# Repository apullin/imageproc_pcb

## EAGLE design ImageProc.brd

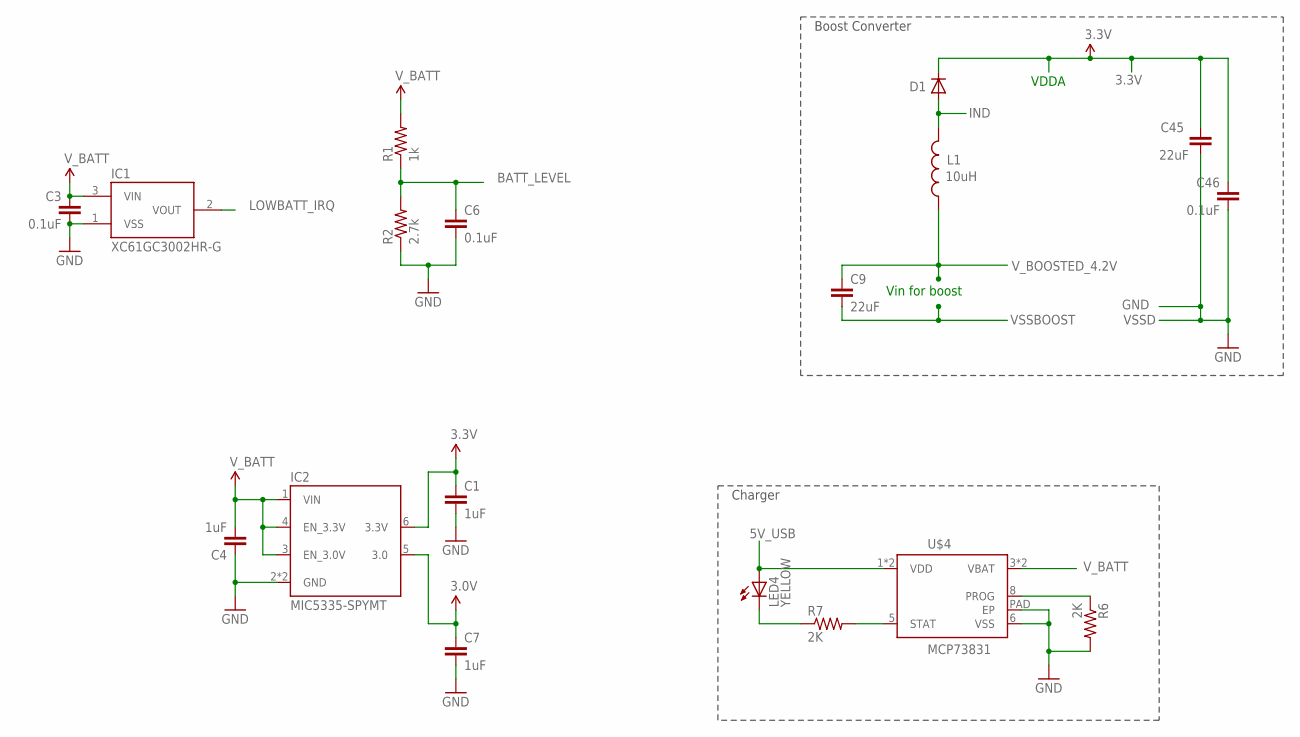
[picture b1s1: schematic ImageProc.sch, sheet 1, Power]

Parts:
C1, C4, C7: 1uF; 0402-CAP
C3, C6, C46: 0.1uF; 0402-CAP
C9, C45: 22uF; 0805
D1: DIODE-SOD123; SOD123
IC1: XC61GC3002HR-G; USP-3
IC2: MIC5335-SPYMT; MLF-6
L1: 10uH; INDUCTOR_SMD_3X3
LED4: YELLOW; LED-0603
R1: 1k; 0402-RES
R2: 2.7k; 0402-RES
R6, R7: 2K; 0402-RES
U$4: MCP73831; DFN-8

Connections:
3.0V: C7.1, IC2.5 (3.0)
3.3V: C1.1, C45.1, C46.1, D1.C, IC2.6 (3.3V); also elsewhere on the board
5V_USB: LED4.A, U$4.1 (VDD), U$4.2 (VDD); also elsewhere on the board
BATT_LEVEL: C6.1, R1.1, R2.2; also elsewhere on the board
GND: C1.2, C3.2, C4.1, C6.2, C7.2, C45.2, C46.2, IC1.1 (VSS), IC2.2 (GND), IC2.EPAD (GND), R2.1, R6.2, U$4.6 (VSS), U$4.PAD (EP); also elsewhere on the board
IND: D1.A, L1.P$2 (2); also elsewhere on the board
LOWBATT_IRQ: IC1.2 (VOUT)
unnamed: R6.1, U$4.8 (PROG)
unnamed: LED4.C, R7.1
unnamed: R7.2, U$4.5 (STAT)
VSSBOOST: C9.2; also elsewhere on the board
V_BATT: C3.1, C4.2, IC1.3 (VIN), IC2.1 (VIN), IC2.3 (EN_3.0V), IC2.4 (EN_3.3V), R1.2, U$4.3 (VBAT), U$4.4 (VBAT); also elsewhere on the board
V_BOOSTED_4.2V: C9.1, L1.P$1 (1); also elsewhere on the board

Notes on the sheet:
Vin for boost
VSSD
VDDA
Boost Converter
Charger

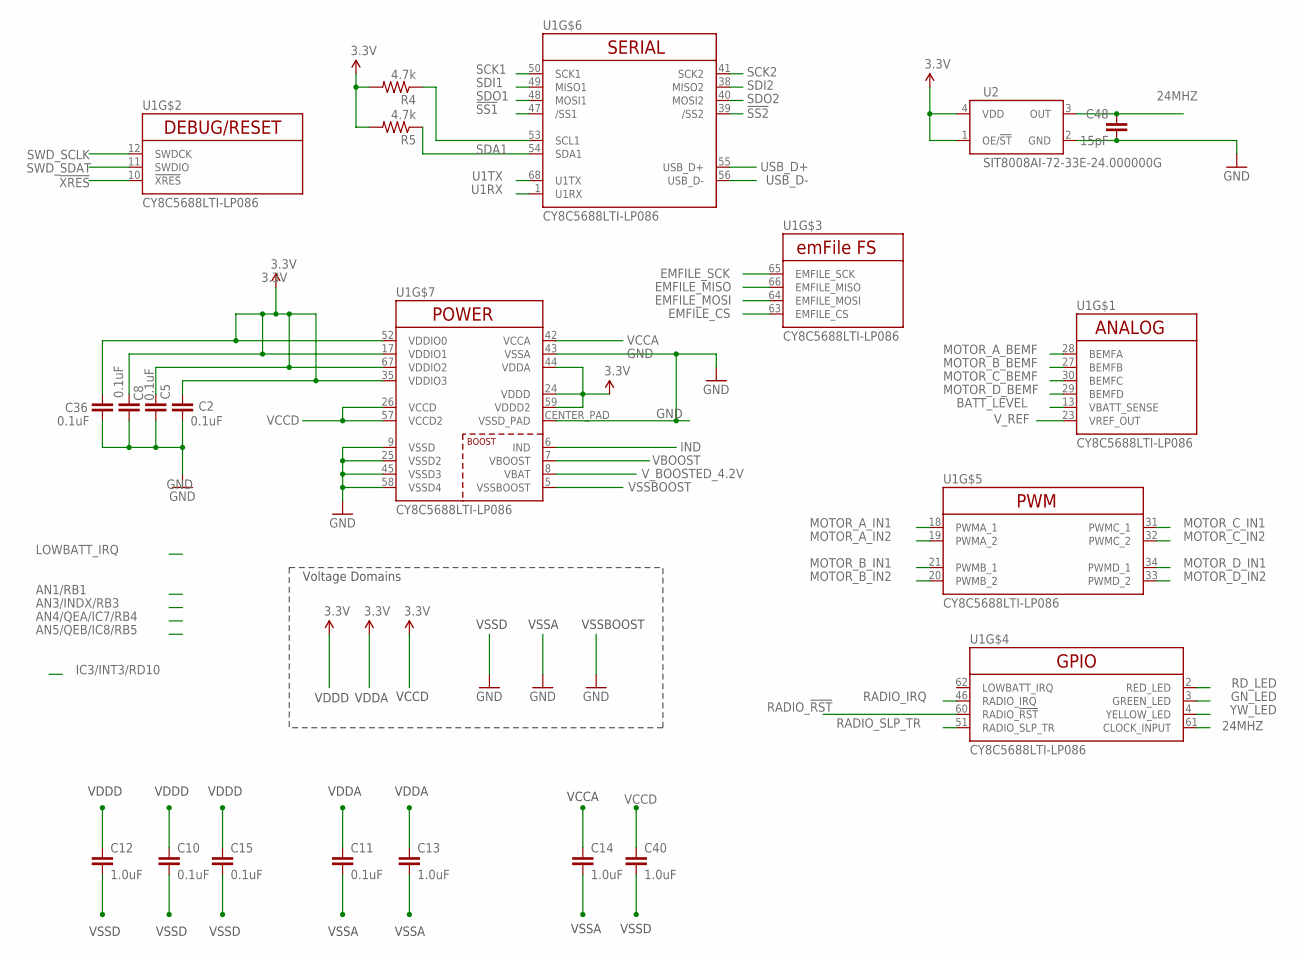
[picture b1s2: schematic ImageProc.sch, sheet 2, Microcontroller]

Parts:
C2, C5, C8, C10, C11, C15, C36: 0.1uF; 0402-CAP
C12, C13, C14, C40: 1.0uF; 0402-CAP
C48: 15pF; 0402-CAP; TOLERANCE 5%; VOLTAGE 50V
R4, R5: 4.7k; 0402-RES
U1: CY8C5688LTI-LP086; 68QFN
U2: SIT8008AI-72-33E-24.000000G; 4-SMD

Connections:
3.3V: C2.1, C5.1, C8.1, C10.1, C11.1, C12.1, C13.1, C15.1, C36.1, R4.2, R5.2, U1.17 (VDDIO1), U1.24 (VDDD), U1.35 (VDDIO3), U1.44 (VDDA), U1.52 (VDDIO0), U1.59 (VDDD2), U1.67 (VDDIO2), U2.1 (OE/!ST), U2.4 (VDD); also elsewhere on the board
24MHZ: C48.1, U1.61 (CLOCK_INPUT), U2.3 (OUT)
!SS1: U1.47 (/SS1); also elsewhere on the board
!SS2: U1.39 (/SS2); also elsewhere on the board
!XRES: U1.10 (!XRES); also elsewhere on the board
BATT_LEVEL: U1.13 (VBATT_SENSE); also elsewhere on the board
EMFILE_CS: U1.63 (EMFILE_CS); also elsewhere on the board
EMFILE_MISO: U1.66 (EMFILE_MISO); also elsewhere on the board
EMFILE_MOSI: U1.64 (EMFILE_MOSI); also elsewhere on the board
EMFILE_SCK: U1.65 (EMFILE_SCK); also elsewhere on the board
GND: C2.2, C5.2, C8.2, C10.2, C11.2, C12.2, C14.2, C15.2, C36.2, C40.2, C48.2, U1.9 (VSSD), U1.25 (VSSD2), U1.43 (VSSA), U1.45 (VSSD3), U1.58 (VSSD4), U1.CENTER_PAD (VSSD_PAD), U2.2 (GND); also elsewhere on the board
GN_LED: U1.3 (GREEN_LED); also elsewhere on the board
IND: U1.6 (IND); also elsewhere on the board
MOTOR_A_BEMF: U1.28 (BEMFA); also elsewhere on the board
MOTOR_A_IN1: U1.18 (PWMA_1); also elsewhere on the board
MOTOR_A_IN2: U1.19 (PWMA_2); also elsewhere on the board
MOTOR_B_BEMF: U1.27 (BEMFB); also elsewhere on the board
MOTOR_B_IN1: U1.21 (PWMB_1); also elsewhere on the board
MOTOR_B_IN2: U1.20 (PWMB_2); also elsewhere on the board
MOTOR_C_BEMF: U1.30 (BEMFC); also elsewhere on the board
MOTOR_C_IN1: U1.31 (PWMC_1); also elsewhere on the board
MOTOR_C_IN2: U1.32 (PWMC_2); also elsewhere on the board
MOTOR_D_BEMF: U1.29 (BEMFD); also elsewhere on the board
MOTOR_D_IN1: U1.34 (PWMD_1); also elsewhere on the board
MOTOR_D_IN2: U1.33 (PWMD_2); also elsewhere on the board
RADIO_!RST: U1.60 (RADIO_!RST); also elsewhere on the board
RADIO_IRQ: U1.46 (RADIO_IRQ); also elsewhere on the board
RADIO_SLP_TR: U1.51 (RADIO_SLP_TR); also elsewhere on the board
RD_LED: U1.2 (RED_LED); also elsewhere on the board
SCK1: U1.50 (SCK1); also elsewhere on the board
SCK2: U1.41 (SCK2); also elsewhere on the board
SCL1: R4.1, U1.53 (SCL1); also elsewhere on the board
SDA1: R5.1, U1.54 (SDA1); also elsewhere on the board
SDI1: U1.49 (MISO1); also elsewhere on the board
SDI2: U1.38 (MISO2); also elsewhere on the board
SDO1: U1.48 (MOSI1); also elsewhere on the board
SDO2: U1.40 (MOSI2); also elsewhere on the board
SWD_SCLK: U1.12 (SWDCK); also elsewhere on the board
SWD_SDAT: U1.11 (SWDIO); also elsewhere on the board
U1RX: U1.1 (U1RX); also elsewhere on the board
U1TX: U1.68 (U1TX); also elsewhere on the board
USB_D+: U1.55 (USB_D+); also elsewhere on the board
USB_D-: U1.56 (USB_D-); also elsewhere on the board
VBOOST: U1.7 (VBOOST)
VCCA: C14.1, U1.42 (VCCA)
VCCD: C40.1, U1.26 (VCCD), U1.57 (VCCD2)
VSSA: C13.2
VSSBOOST: U1.5 (VSSBOOST); also elsewhere on the board
V_BOOSTED_4.2V: U1.8 (VBAT); also elsewhere on the board
V_REF: U1.23 (VREF_OUT); also elsewhere on the board
YW_LED: U1.4 (YELLOW_LED); also elsewhere on the board

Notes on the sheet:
Voltage Domains
VSSA
VSSD
VDDD
VDDA
VCCD
VSSBOOST
VCCA

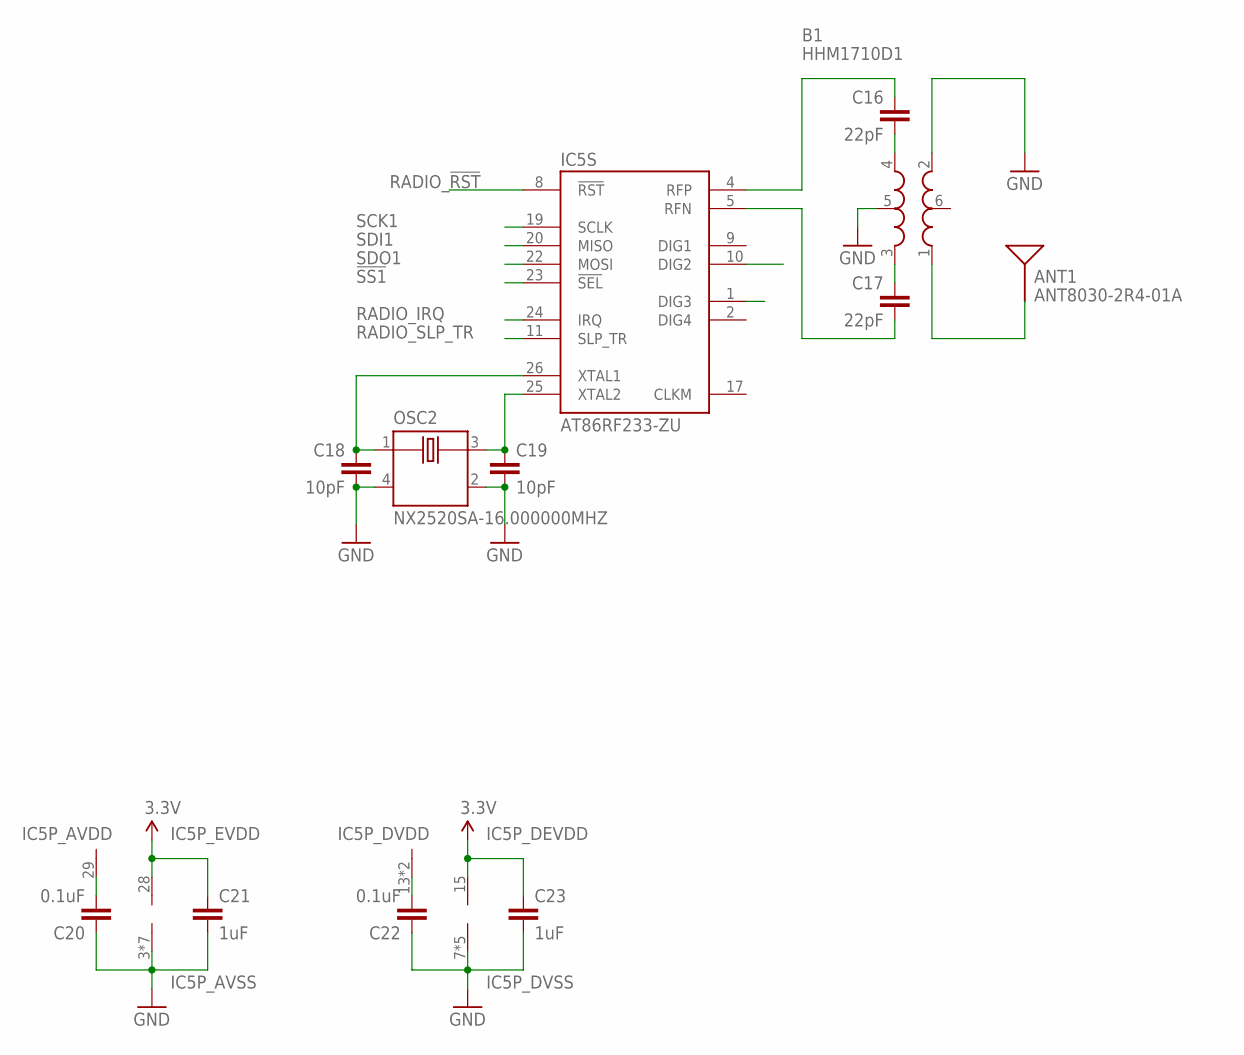
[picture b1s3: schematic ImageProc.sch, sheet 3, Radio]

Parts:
ANT1: ANT8030-2R4-01A
B1: HHM1710D1; 0603-BALUN
C16, C17: 22pF; 0402-CAP; TOLERANCE 5%; VOLTAGE 50V
C18, C19: 10pF; 0402-CAP; TOLERANCE 10%; VOLTAGE 50V
C20, C22: 0.1uF; 0402-CAP; TOLERANCE 10%; VOLTAGE 16V
C21, C23: 1uF; 0402-CAP; TOLERANCE 10%; VOLTAGE 16V
IC5: AT86RF233-ZU; VQFN-32QN2
OSC2: NX2520SA-16.000000MHZ; CRYSTAL-SMD

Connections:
3.3V: C21.1, C23.1, IC5.15 (V+), IC5.28 (V+); also elsewhere on the board
!SS1: IC5.23 (!SEL); also elsewhere on the board
GND: B1.2 (RFGND), B1.5 (GND), C18.2, C19.2, C20.1, C21.2, C22.1, C23.2, IC5.3 (V-), IC5.6 (V-), IC5.7 (V-), IC5.12 (V-), IC5.16 (V-), IC5.18 (V-), IC5.21 (V-), IC5.27 (V-), IC5.30 (V-), IC5.31 (V-), IC5.32 (V-), IC5.PAD (V-), OSC2.2 (GND), OSC2.4 (GND); also elsewhere on the board
unnamed: C22.2, IC5.13 (V+), IC5.14 (V+)
unnamed: C20.2, IC5.29 (V+)
unnamed: ANT1.A, B1.1 (UNBAL)
unnamed: C16.1, IC5.4 (RFP)
unnamed: C17.2, IC5.5 (RFN)
unnamed: C19.1, IC5.25 (XTAL2), OSC2.3 (OUT/IN)
unnamed: C18.1, IC5.26 (XTAL1), OSC2.1 (IN/OUT)
unnamed: B1.3 (BAL3), C17.1
unnamed: B1.4 (BAL4), C16.2
RADIO_!RST: IC5.8 (!RST); also elsewhere on the board
RADIO_IRQ: IC5.24 (IRQ); also elsewhere on the board
RADIO_SLP_TR: IC5.11 (SLP_TR); also elsewhere on the board
SCK1: IC5.19 (SCLK); also elsewhere on the board
SDI1: IC5.20 (MISO); also elsewhere on the board
SDO1: IC5.22 (MOSI); also elsewhere on the board

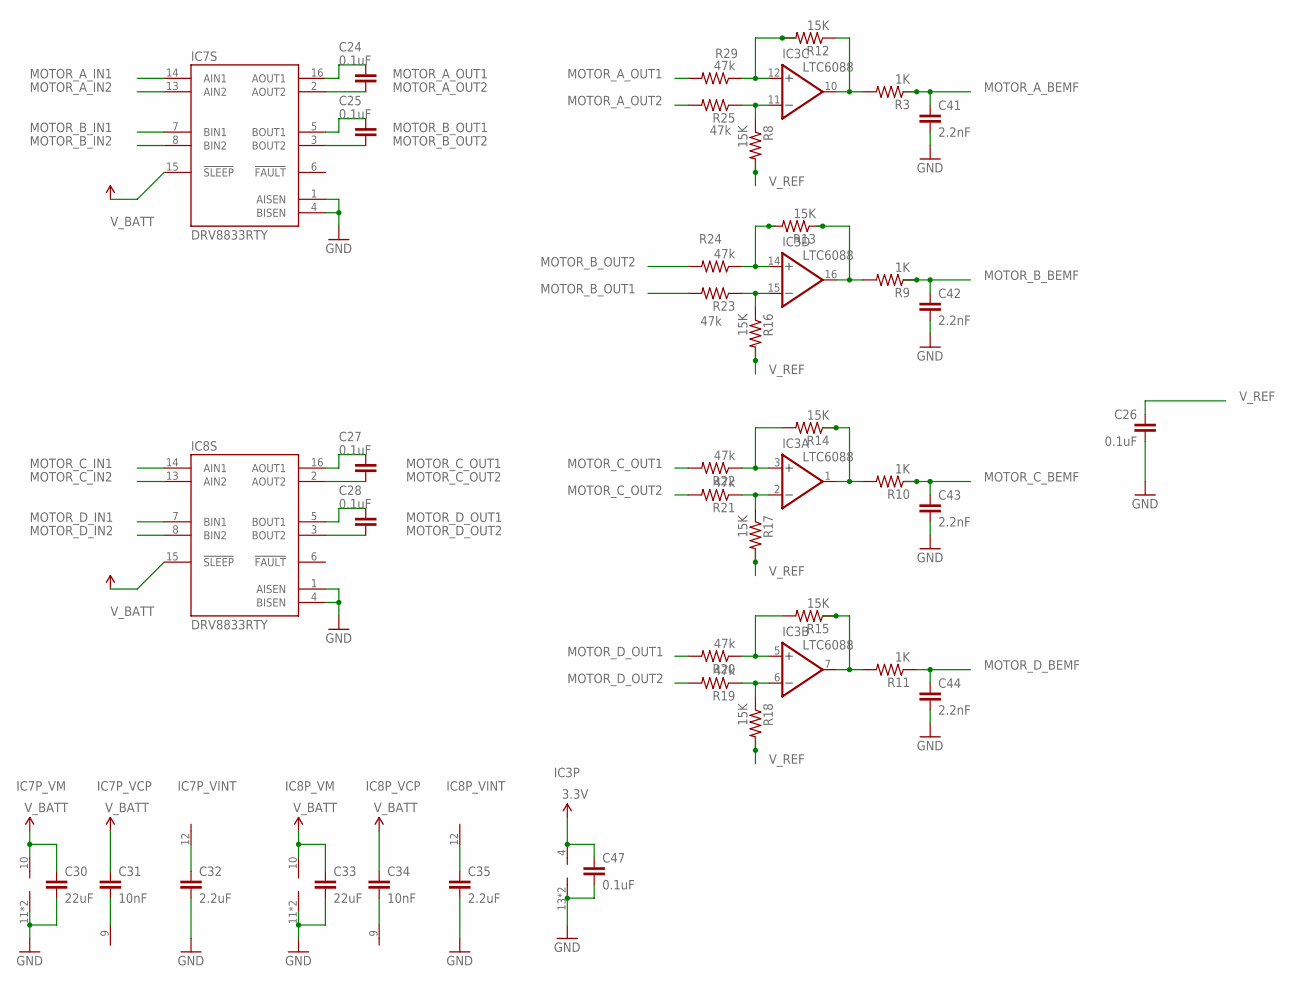
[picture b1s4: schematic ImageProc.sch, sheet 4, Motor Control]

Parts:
C24, C25, C27, C28: 0.1uF; 0402-CAP; VOLTAGE 10V
C26, C47: 0.1uF; 0402-CAP
C30, C33: 22uF; 0603-CAP
C31, C34: 10nF; 0402-CAP; VOLTAGE 16V
C32, C35: 2.2uF; 0402-CAP; VOLTAGE 6.3V
C41, C42, C43, C44: 2.2nF; 0402-CAP
IC3: LTC6088; DFN-16
IC7, IC8: DRV8833RTY; S-PWQFN-N16
R3, R9, R10, R11: 1K; 0402-RES
R8, R12, R13, R14, R15, R16, R17, R18: 15K; 0402-RES
R19, R20, R21, R22, R23, R24, R25, R29: 47k; 0402-RES

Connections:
3.3V: C47.1, IC3.4 (V+); also elsewhere on the board
GND: C26.2, C30.2, C32.2, C33.2, C35.2, C41.2, C42.2, C43.2, C44.2, C47.2, IC3.13 (V-), IC3.PAD (V-), IC7.1 (AISEN), IC7.4 (BISEN), IC7.11 (V-), IC7.PPAD (V-), IC8.1 (AISEN), IC8.4 (BISEN), IC8.11 (V-), IC8.PPAD (V-); also elsewhere on the board
MOTOR_A_BEMF: C41.1, R3.1; also elsewhere on the board
MOTOR_A_IN1: IC7.14 (AIN1); also elsewhere on the board
MOTOR_A_IN2: IC7.13 (AIN2); also elsewhere on the board
MOTOR_A_OUT1: C24.1, IC7.16 (AOUT1), R29.2; also elsewhere on the board
MOTOR_A_OUT2: C24.2, IC7.2 (AOUT2), R25.2; also elsewhere on the board
MOTOR_B_BEMF: C42.1, R9.1; also elsewhere on the board
MOTOR_B_IN1: IC7.7 (BIN1); also elsewhere on the board
MOTOR_B_IN2: IC7.8 (BIN2); also elsewhere on the board
MOTOR_B_OUT1: C25.1, IC7.5 (BOUT1), R23.2; also elsewhere on the board
MOTOR_B_OUT2: C25.2, IC7.3 (BOUT2), R24.2; also elsewhere on the board
MOTOR_C_BEMF: C43.1, R10.1; also elsewhere on the board
MOTOR_C_IN1: IC8.14 (AIN1); also elsewhere on the board
MOTOR_C_IN2: IC8.13 (AIN2); also elsewhere on the board
MOTOR_C_OUT1: C27.1, IC8.16 (AOUT1), R22.2; also elsewhere on the board
MOTOR_C_OUT2: C27.2, IC8.2 (AOUT2), R21.2; also elsewhere on the board
MOTOR_D_BEMF: C44.1, R11.1; also elsewhere on the board
MOTOR_D_IN1: IC8.7 (BIN1); also elsewhere on the board
MOTOR_D_IN2: IC8.8 (BIN2); also elsewhere on the board
MOTOR_D_OUT1: C28.1, IC8.5 (BOUT1), R20.2; also elsewhere on the board
MOTOR_D_OUT2: C28.2, IC8.3 (BOUT2), R19.2; also elsewhere on the board
unnamed: C31.2, IC7.9 (V+)
unnamed: C32.1, IC7.12 (V-)
unnamed: C34.2, IC8.9 (V+)
unnamed: C35.1, IC8.12 (V-)
unnamed: IC3.14 (+IN), R13.2, R24.1
unnamed: IC3.15 (-IN), R16.1, R23.1
unnamed: IC3.3 (+IN), R14.2, R22.1
unnamed: IC3.2 (-IN), R17.1, R21.1
unnamed: IC3.5 (+IN), R15.2, R20.1
unnamed: IC3.6 (-IN), R18.1, R19.1
unnamed: IC3.12 (+IN), R12.2, R29.1
unnamed: IC3.11 (-IN), R8.1, R25.1
unnamed: IC3.7 (OUT), R11.2, R15.1
unnamed: IC3.1 (OUT), R10.2, R14.1
unnamed: IC3.10 (OUT), R3.2, R12.1
unnamed: IC3.16 (OUT), R9.2, R13.1
V_BATT: C30.1, C31.1, C33.1, C34.1, IC7.10 (V+), IC7.15 (!SLEEP), IC8.10 (V+), IC8.15 (!SLEEP); also elsewhere on the board
V_REF: C26.1, R8.2, R16.2, R17.2, R18.2; also elsewhere on the board

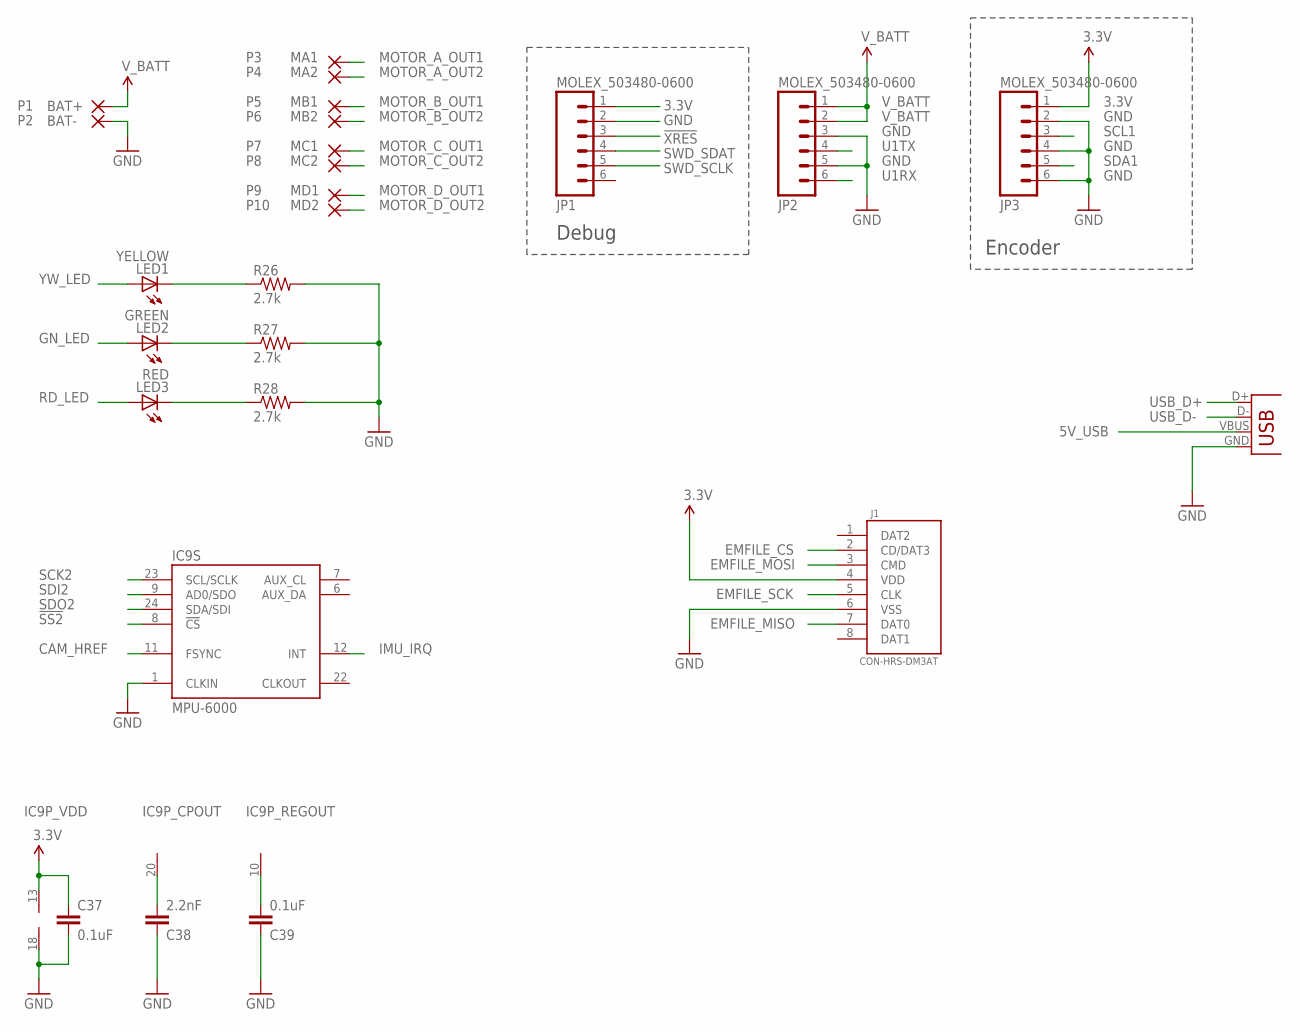
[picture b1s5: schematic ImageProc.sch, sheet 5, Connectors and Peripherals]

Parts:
C37: 0.1uF; 0402-CAP; TOLERANCE 10%; VOLTAGE 4V
C38: 2.2nF; 0402-CAP; TOLERANCE 10%; VOLTAGE 50V
C39: 0.1uF; 0402-CAP; TOLERANCE 10%; VOLTAGE 2V
IC9: MPU-6000; QFN-24
J1: CON-HRS-DM3AT; HRS-DM3AT
JP1, JP2, JP3: MOLEX_503480-0600
JP6: USBSMD; USB-MINIB
LED1: YELLOW; LED-0603
LED2: GREEN; LED-0603
LED3: RED; LED-0603
P1: BAT+; SMD1,27-2,54
P2: BAT-; SMD1,27-2,54
P3: MA1; SMD1,27-2,54
P4: MA2; SMD1,27-2,54
P5: MB1; SMD1,27-2,54
P6: MB2; SMD1,27-2,54
P7: MC1; SMD1,27-2,54
P8: MC2; SMD1,27-2,54
P9: MD1; SMD1,27-2,54
P10: MD2; SMD1,27-2,54
R26, R27, R28: 2.7k; 0402-RES

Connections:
3.3V: C37.1, IC9.13 (V+), J1.4 (VDD), JP1.1, JP3.1; also elsewhere on the board
5V_USB: JP6.VBUS; also elsewhere on the board
!SS2: IC9.8 (!CS); also elsewhere on the board
!XRES: JP1.3; also elsewhere on the board
CAM_HREF: IC9.11 (FSYNC)
EMFILE_CS: J1.2 (CD/DAT3); also elsewhere on the board
EMFILE_MISO: J1.7 (DAT0); also elsewhere on the board
EMFILE_MOSI: J1.3 (CMD); also elsewhere on the board
EMFILE_SCK: J1.5 (CLK); also elsewhere on the board
GND: C37.2, C38.1, C39.1, IC9.1 (CLKIN), IC9.18 (V-), J1.6 (VSS), JP1.2, JP2.3, JP2.5, JP3.2, JP3.4, JP3.6, JP6.GND, P2.1, R26.2, R27.2, R28.2; also elsewhere on the board
GN_LED: LED2.A; also elsewhere on the board
IMU_IRQ: IC9.12 (INT)
MOTOR_A_OUT1: P3.1; also elsewhere on the board
MOTOR_A_OUT2: P4.1; also elsewhere on the board
MOTOR_B_OUT1: P5.1; also elsewhere on the board
MOTOR_B_OUT2: P6.1; also elsewhere on the board
MOTOR_C_OUT1: P7.1; also elsewhere on the board
MOTOR_C_OUT2: P8.1; also elsewhere on the board
MOTOR_D_OUT1: P9.1; also elsewhere on the board
MOTOR_D_OUT2: P10.1; also elsewhere on the board
unnamed: LED1.C, R26.1
unnamed: LED2.C, R27.1
unnamed: LED3.C, R28.1
unnamed: C38.2, IC9.20 (V-)
unnamed: C39.2, IC9.10 (V-)
RD_LED: LED3.A; also elsewhere on the board
SCK2: IC9.23 (SCL/SCLK); also elsewhere on the board
SCL1: JP3.3; also elsewhere on the board
SDA1: JP3.5; also elsewhere on the board
SDI2: IC9.9 (AD0/SDO); also elsewhere on the board
SDO2: IC9.24 (SDA/SDI); also elsewhere on the board
SWD_SCLK: JP1.5; also elsewhere on the board
SWD_SDAT: JP1.4; also elsewhere on the board
U1RX: JP2.6; also elsewhere on the board
U1TX: JP2.4; also elsewhere on the board
USB_D+: JP6.D+; also elsewhere on the board
USB_D-: JP6.D-; also elsewhere on the board
V_BATT: JP2.1, JP2.2, P1.1; also elsewhere on the board
YW_LED: LED1.A; also elsewhere on the board

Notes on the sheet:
Encoder
Debug

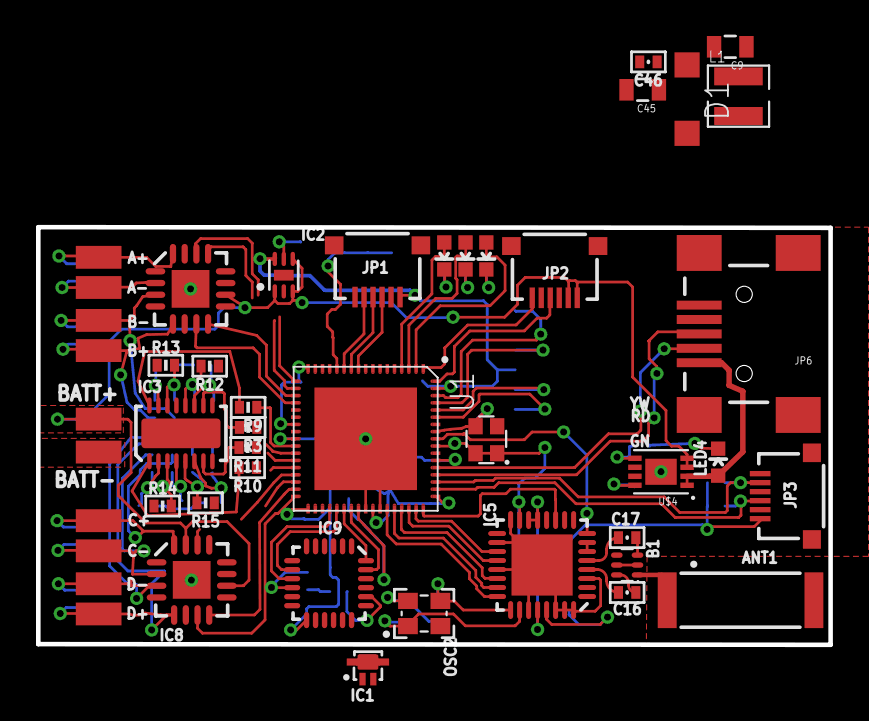
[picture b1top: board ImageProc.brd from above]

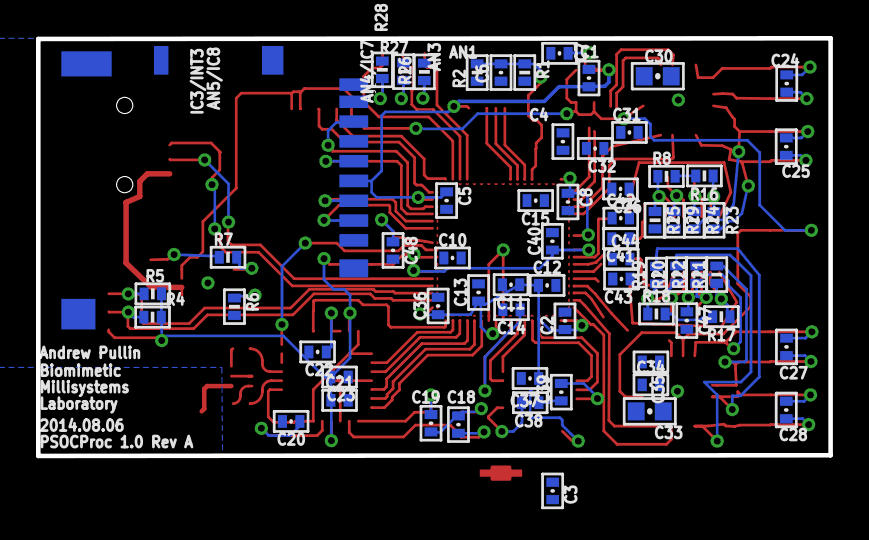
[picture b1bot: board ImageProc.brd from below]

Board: 2 copper layers, 44.0 x 23.2 mm, 110 parts (64 on the bottom side), 93 nets.

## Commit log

2014-07-16 Initial replacement of dsPIC with STM32 chip in schematic.
2014-08-06 Updating git ignore to not include doc folder
2014-08-06 Initial strip of the IP2.5 Rev C board. dsPic and camera connector removed.
2014-08-13 Initial placement of part with fixed functon pins in place, other pins as placeholders. Library part now active.
2014-08-14 Removed flash, ripping up more routing, added SD card
2014-08-15 Still removing small elemets from existing IP2.5
2014-08-17 Changed to resistor arrays. SD card footprint updated. Much routing removed.
2014-08-19 Major board layout jumble. Lots of placeholder connections.
2014-08-19 Power routing now in schematic. Prelim boost converter components.
2014-08-20 Proof of concept: signal routing for radio, gyro, and debug port into PSOC arbitrary pins.
2014-08-20 Further routing. Moved 1K resistors to res array.
2014-08-21 Fiting .b#* entry in .gitignore
2014-08-26 More routing done. Many voltage domains merged to 3.3v and GND.
2014-08-27 More routing. Starting to use rough paths just to set topology.

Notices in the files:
parts and their libraries:
SparkFun-Connectors: Licensing: Creative Commons ShareAlike 4.0 International - https://creativecommons.org/licenses/by-sa/4.0
biomimetic: UC Regents. All rights reserved.
